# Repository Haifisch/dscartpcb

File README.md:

# NDS-Breakout-Board
A Nintendo DS Cartridge breakout board

## ~~Designed with KiCad~~
this was a fork of pedro's design until, threw his design out with kicad. pulled out my calipers and redesigned from scratch in Autodesk instead. 

(Thank you amcjen for teaching me EAGLE all those years ago <3)

A cartridge with various rumored official uses, known as the DUMMY or kiosk cartridge. My best guess is calling it a kiosk cartridge is a misnomer, usually sold alongside "factory kiosk units" which are known to be seen in testing jigs for the 3DS series from documentation. It was likely used in the factory and even maybe stems from an internally used design that helped prototype the original DS units, who knows.

Ideally, sniffing traffic from a live cartridge would be cool. So, using 5949T62 Spring Probes, a top board to serve as a bed for the cartridge and a bottom board to break the cartridge pins out to test points or to the FPC header. Using the FPC header with PEPCART should allow you to connect the cartridge in the bed to a live console and use the test points as a sniffing point of contact. There's a 3D printable design, needs some rework, handed it off to someone else months ago for redesign but eh no progress afaik. Pogo pin alignment should be damn near perfect with a cartridge, so if the plastic bed around it can hold it in place with something to put contact pressure down on the cartridge (even tape) then the whole thing should be okay. 

Anyways, the design is simple, provided for-free and as open source as I can make it. 

'PEPCART' essentially copies that DUMMY cartridge design. Spent a long night searching for a matching FPC connector and found the Würth Elektronik 687120183622.

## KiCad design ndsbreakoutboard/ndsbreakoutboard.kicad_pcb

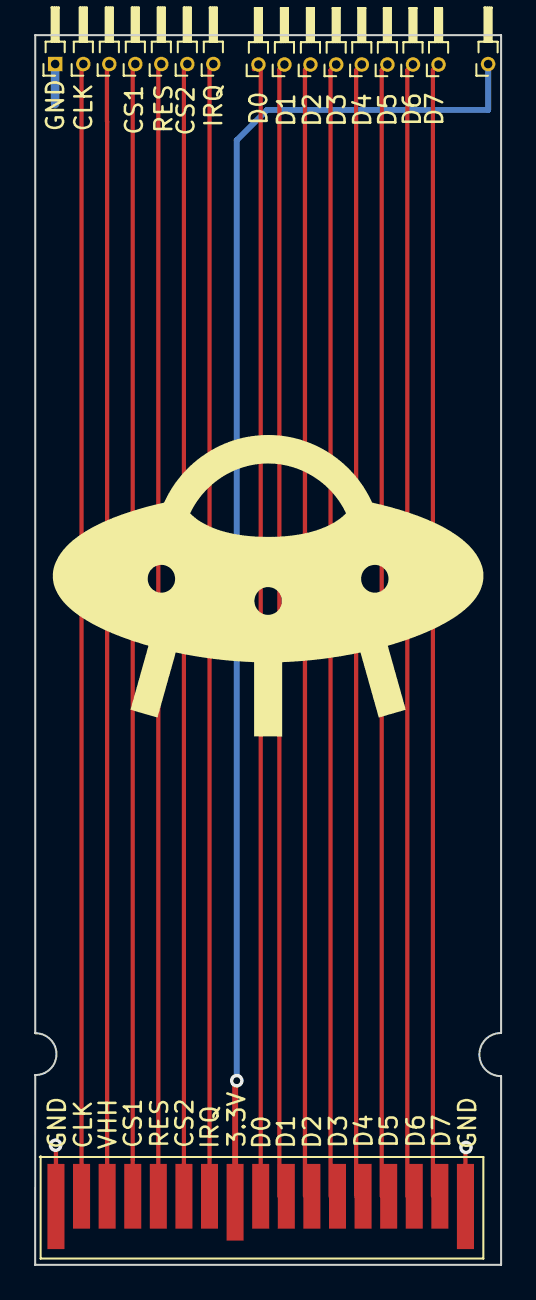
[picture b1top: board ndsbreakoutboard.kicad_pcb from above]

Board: 2 copper layers, 27.3 x 72.1 mm, 17 parts (0 on the bottom side), 16 nets.

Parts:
3.3V: Conn_01x01_Female; PinHeader_1x01_P1.00mm_Horizontal
CLK: Conn_01x01_Female; PinHeader_1x01_P1.00mm_Horizontal
CS1, CS2: Conn_01x01_Female; PinHeader_1x01_P1.00mm_Horizontal
D0, D1, D2, D3, D4, D5, D6, D7: Conn_01x01_Female; PinHeader_1x01_P1.00mm_Horizontal
GND: Conn_01x01_Female; PinHeader_1x01_P1.00mm_Horizontal
IRQ: Conn_01x01_Female; PinHeader_1x01_P1.00mm_Horizontal
J14: Conn_01x01_Female; PinHeader_1x01_P1.00mm_Horizontal
RES: Conn_01x01_Female; PinHeader_1x01_P1.00mm_Horizontal
U1: ndsPADS; nds_contact_pads

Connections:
unnamed: GND.1, U1.1, U1.17
unnamed: CLK.1, U1.2
unnamed: CS1.1, U1.4
unnamed: RES.1, U1.5
unnamed: CS2.1, U1.6
unnamed: IRQ.1, U1.7
unnamed: D0.1, U1.9
unnamed: D1.1, U1.10
unnamed: D2.1, U1.11
unnamed: D3.1, U1.12
unnamed: D4.1, U1.13
unnamed: D5.1, U1.14
unnamed: D6.1, U1.15
unnamed: D7.1, U1.16
unnamed: J14.1, U1.3
unnamed: 3.3V.1, U1.8

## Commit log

2022-11-10 rough push
2023-05-22 Empires collapse waiting for the dspico cartridge
